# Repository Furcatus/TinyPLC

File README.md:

# TinyPLC

NOTE: This project is under construction. Do not expect everything to work just yet.

## What is it?
This project provides a small and easy-to-use open-source PLC (programmable logic controller) hardware / software platform intended for small automation and control tasks, built around a Raspberry Pi Pico 2W.

## Who is it for?
TinyPLC aims towards hobbyist developers and electrical engineers who want to easily automate stuff in the physical world with Python, but have been limited due to the lack of peripheral hardware connected to their microcontrollers, until now!

### Hardware features:
- 5V supply voltage
- 4 isolated digital inputs (5V to 24V, isolated external 5V supply through DC/DC converter)
- 4 relay outputs (contact: NO, up to 230V, 10A)
- SPI interface
- I²C interface
- 6 GPIOs (3,3V)
- custom 3D printable enclosure

### Software features:
- controller programmed in MicroPython
- slim PLC framework with user-defined initialization and loop function
- open-source
- possibility to use the WiFi/Bluetooth capabilities of the used Rasperry Pi Pico 2W board to build your own wireless controller

## License and Disclaimer
This project is released under the MIT license. Feel free to use it for your projects, as long as you know what you are doing when dealing with electrics/electronics. I am not liable to any harm you are causing to yourself, others or someone's property when using the provided files. Do not use TinyPLC with dangerous voltages or for safety-critical applications and follow the regulations and laws applicable in your location!

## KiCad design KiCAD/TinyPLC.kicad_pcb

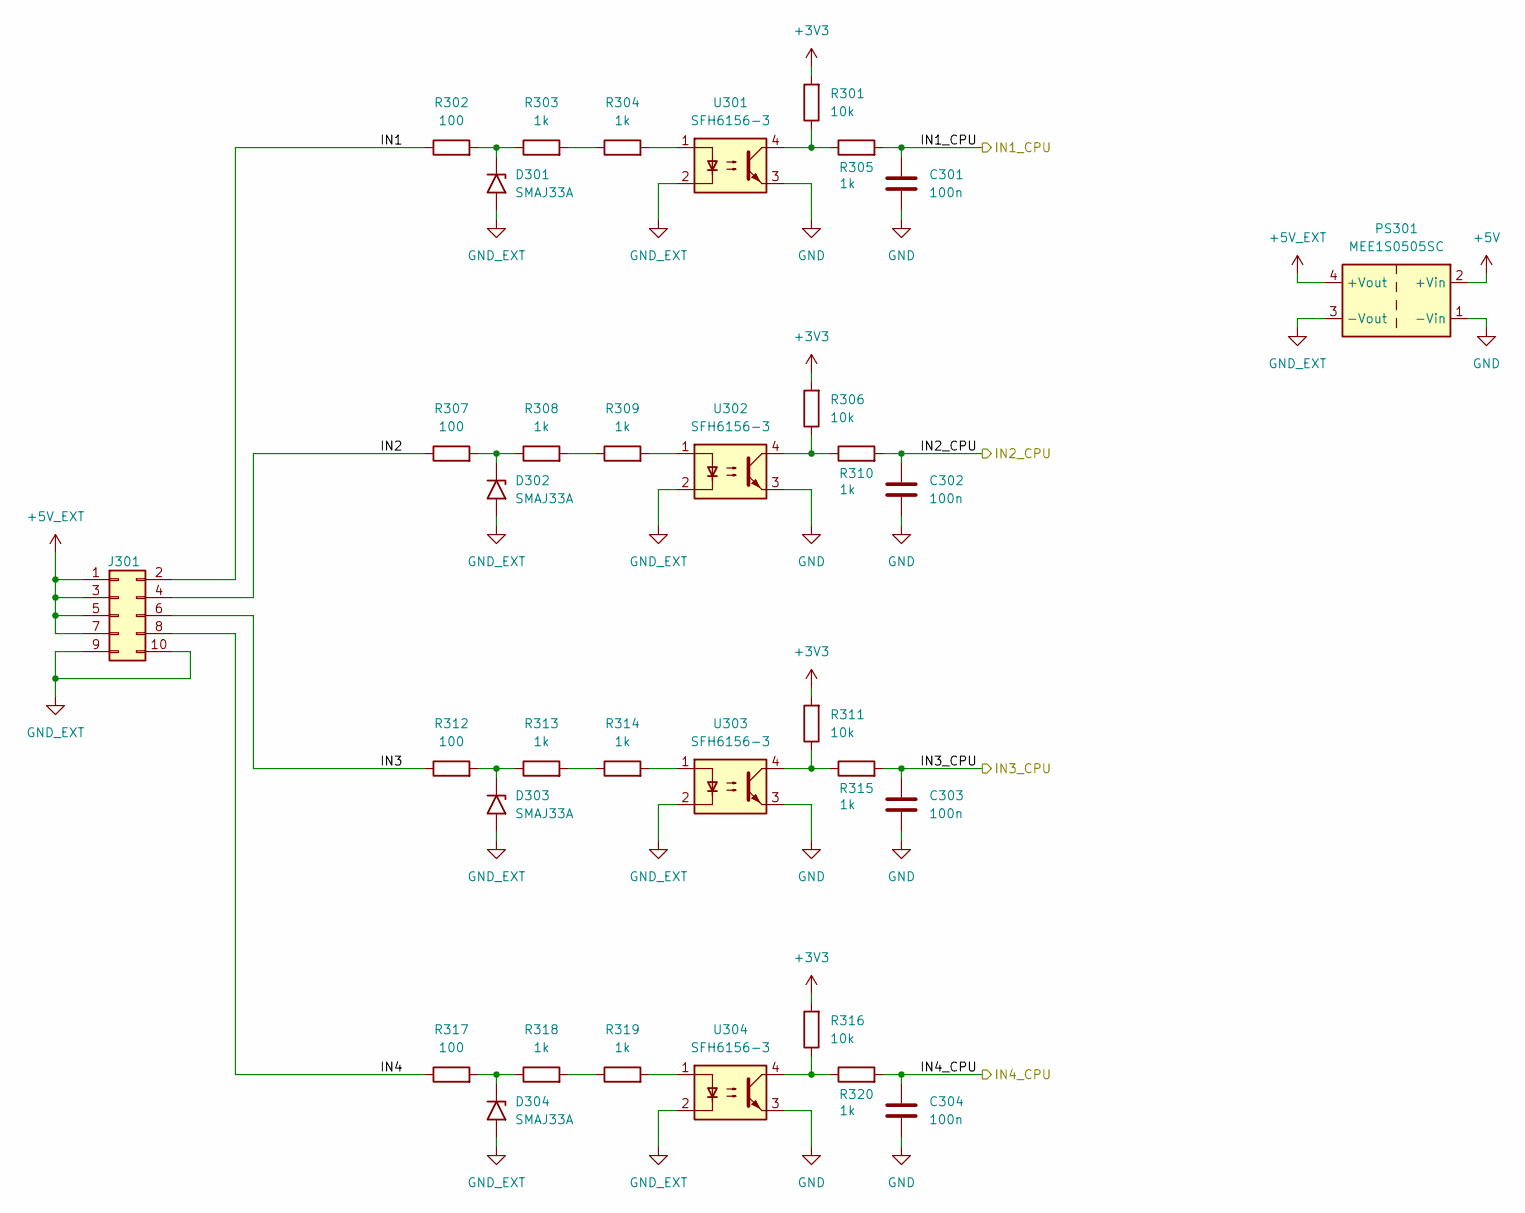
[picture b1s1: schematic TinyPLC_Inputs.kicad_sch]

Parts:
C301, C302, C303, C304: 100n; C_0603_1608Metric_Pad1.08x0.95mm_HandSolder
D301, D302, D303, D304: SMAJ33A; D_SMA
J301: S2L 3.50/10/180G 3.5SN OR BX; Weidmüller_S2L_2x05_3.50mm
PS301: MEE1S0505SC; Converter_DCDC_Murata_MEE1SxxxxSC_THT
R301, R306, R311, R316: 10k; R_0603_1608Metric_Pad0.98x0.95mm_HandSolder
R302, R307, R312, R317: 100; R_MiniMELF_MMA-0204
R303, R304, R308, R309, R313, R314, R318, R319: 1k; R_1206_3216Metric_Pad1.30x1.75mm_HandSolder
R305, R310, R315, R320: 1k; R_0603_1608Metric_Pad0.98x0.95mm_HandSolder
U301, U302, U303, U304: SFH6156-3; DIP-4_W7.62mm_SMDSocket_SmallPads

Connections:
+3V3: R301.2, R306.2, R311.2, R316.2; also elsewhere on the board
+5V: PS301.2 (+Vin); also elsewhere on the board
+5V_EXT: J301.1, J301.3, J301.5, J301.7, PS301.4 (+Vout)
/Controller/IN1_CPU: C301.1, R305.2; also elsewhere on the board
/Controller/IN2_CPU: C302.1, R310.2; also elsewhere on the board
/Controller/IN3_CPU: C303.1, R315.2; also elsewhere on the board
/Controller/IN4_CPU: C304.1, R320.2; also elsewhere on the board
/Inputs/IN1: J301.2, R302.1
/Inputs/IN2: J301.4, R307.1
/Inputs/IN3: J301.6, R312.1
/Inputs/IN4: J301.8, R317.1
GND: C301.2, C302.2, C303.2, C304.2, PS301.1 (-Vin), U301.3, U302.3, U303.3, U304.3; also elsewhere on the board
GND_EXT: D301.2 (A2), D302.2 (A2), D303.2 (A2), D304.2 (A2), J301.9, J301.10, PS301.3 (-Vout), U301.2, U302.2, U303.2, U304.2
unnamed: D301.1 (A1), R302.2, R303.1
unnamed: D302.1 (A1), R307.2, R308.1
unnamed: D303.1 (A1), R312.2, R313.1
unnamed: D304.1 (A1), R317.2, R318.1
unnamed: R301.1, R305.1, U301.4
unnamed: R303.2, R304.1
unnamed: R304.2, U301.1
unnamed: R306.1, R310.1, U302.4
unnamed: R308.2, R309.1
unnamed: R309.2, U302.1
unnamed: R311.1, R315.1, U303.4
unnamed: R313.2, R314.1
unnamed: R314.2, U303.1
unnamed: R316.1, R320.1, U304.4
unnamed: R318.2, R319.1
unnamed: R319.2, U304.1

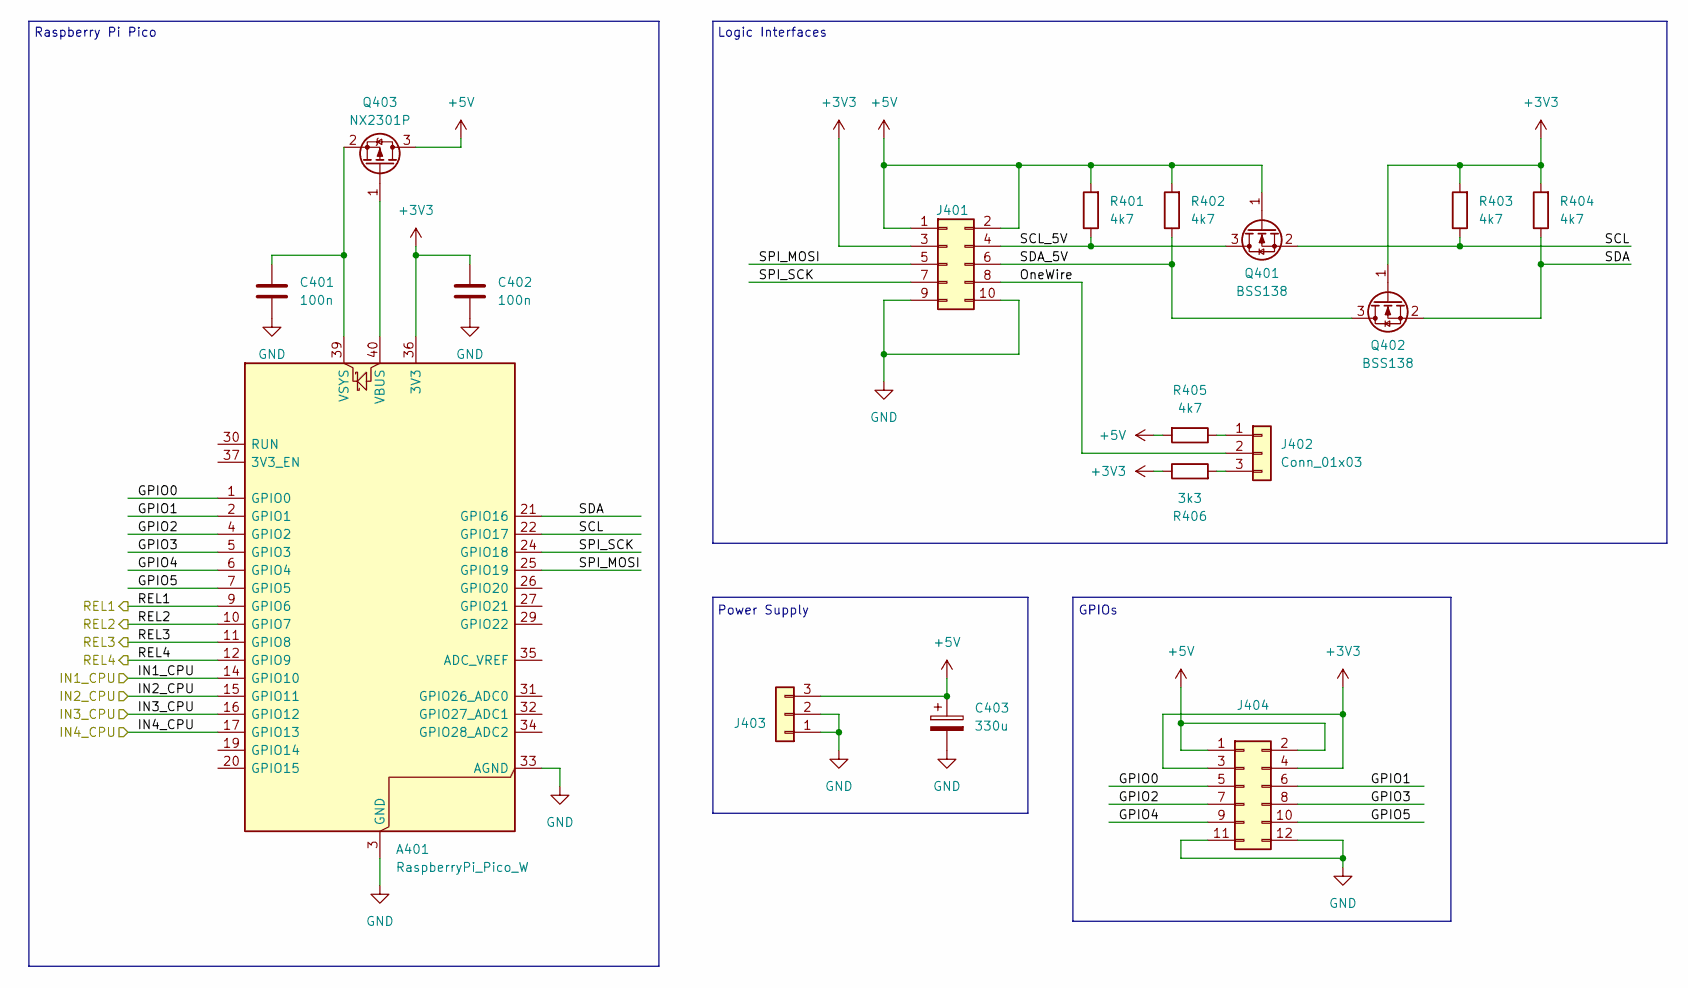
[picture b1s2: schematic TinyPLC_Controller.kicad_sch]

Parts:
A401: RaspberryPi_Pico_W; RaspberryPi_Pico_Common_SMD
C401, C402: 100n; C_0603_1608Metric_Pad1.08x0.95mm_HandSolder
C403: 330u; CP_Elec_6.3x5.9
J401: S2L 3.50/10/180G 3.5SN OR BX; Weidmüller_S2L_2x05_3.50mm
J402: Conn_01x03; PinHeader_1x03_P2.54mm_Vertical
J403: S2L 3.50/03/180G 3.2SN OR BX; Weidmüller_S2L_1x03_3.50mm
J404: Conn_02x06_Odd_Even; PinSocket_2x06_P2.54mm_Vertical
Q401, Q402: BSS138; SOT-23-3
Q403: NX2301P; SOT-23
R401, R402, R403, R404, R405: 4k7; R_0603_1608Metric_Pad0.98x0.95mm_HandSolder
R406: 3k3; R_0603_1608Metric_Pad0.98x0.95mm_HandSolder

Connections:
+3V3: A401.36 (3V3), C402.1, J401.3, J404.3, J404.4, Q402.1 (G), R403.2, R404.2, R406.1; also elsewhere on the board
+5V: C403.1, J401.1, J401.2, J403.3, J404.1, J404.2, Q401.1 (G), Q403.3 (D), R401.2, R402.2, R405.2; also elsewhere on the board
/Controller/GPIO0: A401.1 (GPIO0), J404.5
/Controller/GPIO1: A401.2 (GPIO1), J404.6
/Controller/GPIO2: A401.4 (GPIO2), J404.7
/Controller/GPIO3: A401.5 (GPIO3), J404.8
/Controller/GPIO4: A401.6 (GPIO4), J404.9
/Controller/GPIO5: A401.7 (GPIO5), J404.10
/Controller/IN1_CPU: A401.14 (GPIO10); also elsewhere on the board
/Controller/IN2_CPU: A401.15 (GPIO11); also elsewhere on the board
/Controller/IN3_CPU: A401.16 (GPIO12); also elsewhere on the board
/Controller/IN4_CPU: A401.17 (GPIO13); also elsewhere on the board
/Controller/OneWire: J401.8, J402.2
/Controller/REL1: A401.9 (GPIO6); also elsewhere on the board
/Controller/REL2: A401.10 (GPIO7); also elsewhere on the board
/Controller/REL3: A401.11 (GPIO8); also elsewhere on the board
/Controller/REL4: A401.12 (GPIO9); also elsewhere on the board
/Controller/SCL: A401.22 (GPIO17), Q401.2 (S), R403.1
/Controller/SCL_5V: J401.4, Q401.3 (D), R401.1
/Controller/SDA: A401.21 (GPIO16), Q402.2 (S), R404.1
/Controller/SDA_5V: J401.6, Q402.3 (D), R402.1
/Controller/SPI_MOSI: A401.25 (GPIO19), J401.5
/Controller/SPI_SCK: A401.24 (GPIO18), J401.7
GND: A401.3 (GND), A401.8 (GND), A401.13 (GND), A401.18 (GND), A401.23 (GND), A401.28 (GND), A401.33 (AGND), A401.38 (GND), C401.2, C402.2, C403.2, J401.9, J401.10, J403.1, J403.2, J404.11, J404.12; also elsewhere on the board
unnamed: A401.40 (VBUS), Q403.1 (G)
unnamed: A401.39 (VSYS), C401.1, Q403.2 (S)
unnamed: J402.1, R405.1
unnamed: J402.3, R406.2

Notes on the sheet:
Power Supply
GPIOs
Logic Interfaces
Raspberry Pi Pico

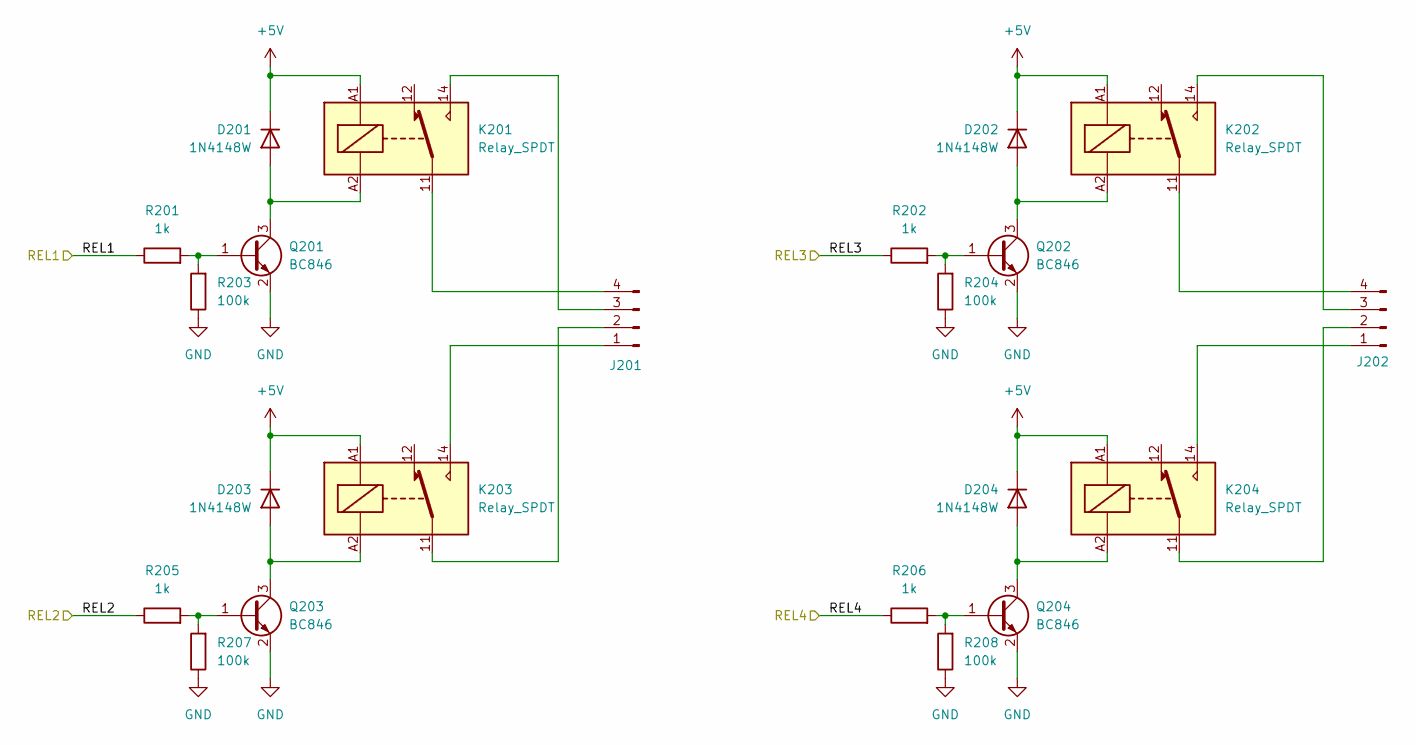
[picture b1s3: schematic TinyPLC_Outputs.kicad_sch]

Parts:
D201, D202, D203, D204: 1N4148W; D_SOD-123
J201, J202: Conn_01x04_Pin; PhoenixContact_MSTBVA_2,5_4-G-5,08_1x04_P5.08mm_Vertical
K201, K202, K203, K204: Relay_SPDT; Relay_SPDT_Hongfa_HF118F
Q201, Q202, Q203, Q204: BC846; SOT-23-3
R201, R202, R205, R206: 1k; R_0603_1608Metric_Pad0.98x0.95mm_HandSolder
R203, R204, R207, R208: 100k; R_0603_1608Metric_Pad0.98x0.95mm_HandSolder

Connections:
+5V: D201.1 (K), D202.1 (K), D203.1 (K), D204.1 (K), K201.A1, K202.A1, K203.A1, K204.A1; also elsewhere on the board
/Controller/REL1: R201.1; also elsewhere on the board
/Controller/REL2: R205.1; also elsewhere on the board
/Controller/REL3: R202.1; also elsewhere on the board
/Controller/REL4: R206.1; also elsewhere on the board
GND: Q201.2 (E), Q202.2 (E), Q203.2 (E), Q204.2 (E), R203.1, R204.1, R207.1, R208.1; also elsewhere on the board
unnamed: D201.2 (A), K201.A2, Q201.3 (C)
unnamed: D202.2 (A), K202.A2, Q202.3 (C)
unnamed: D203.2 (A), K203.A2, Q203.3 (C)
unnamed: D204.2 (A), K204.A2, Q204.3 (C)
unnamed: J201.1, K203.14
unnamed: J201.2, K203.11
unnamed: J201.3, K201.14
unnamed: J201.4, K201.11
unnamed: J202.1, K204.14
unnamed: J202.2, K204.11
unnamed: J202.3, K202.14
unnamed: J202.4, K202.11
unnamed: Q201.1 (B), R201.2, R203.2
unnamed: Q202.1 (B), R202.2, R204.2
unnamed: Q203.1 (B), R205.2, R207.2
unnamed: Q204.1 (B), R206.2, R208.2

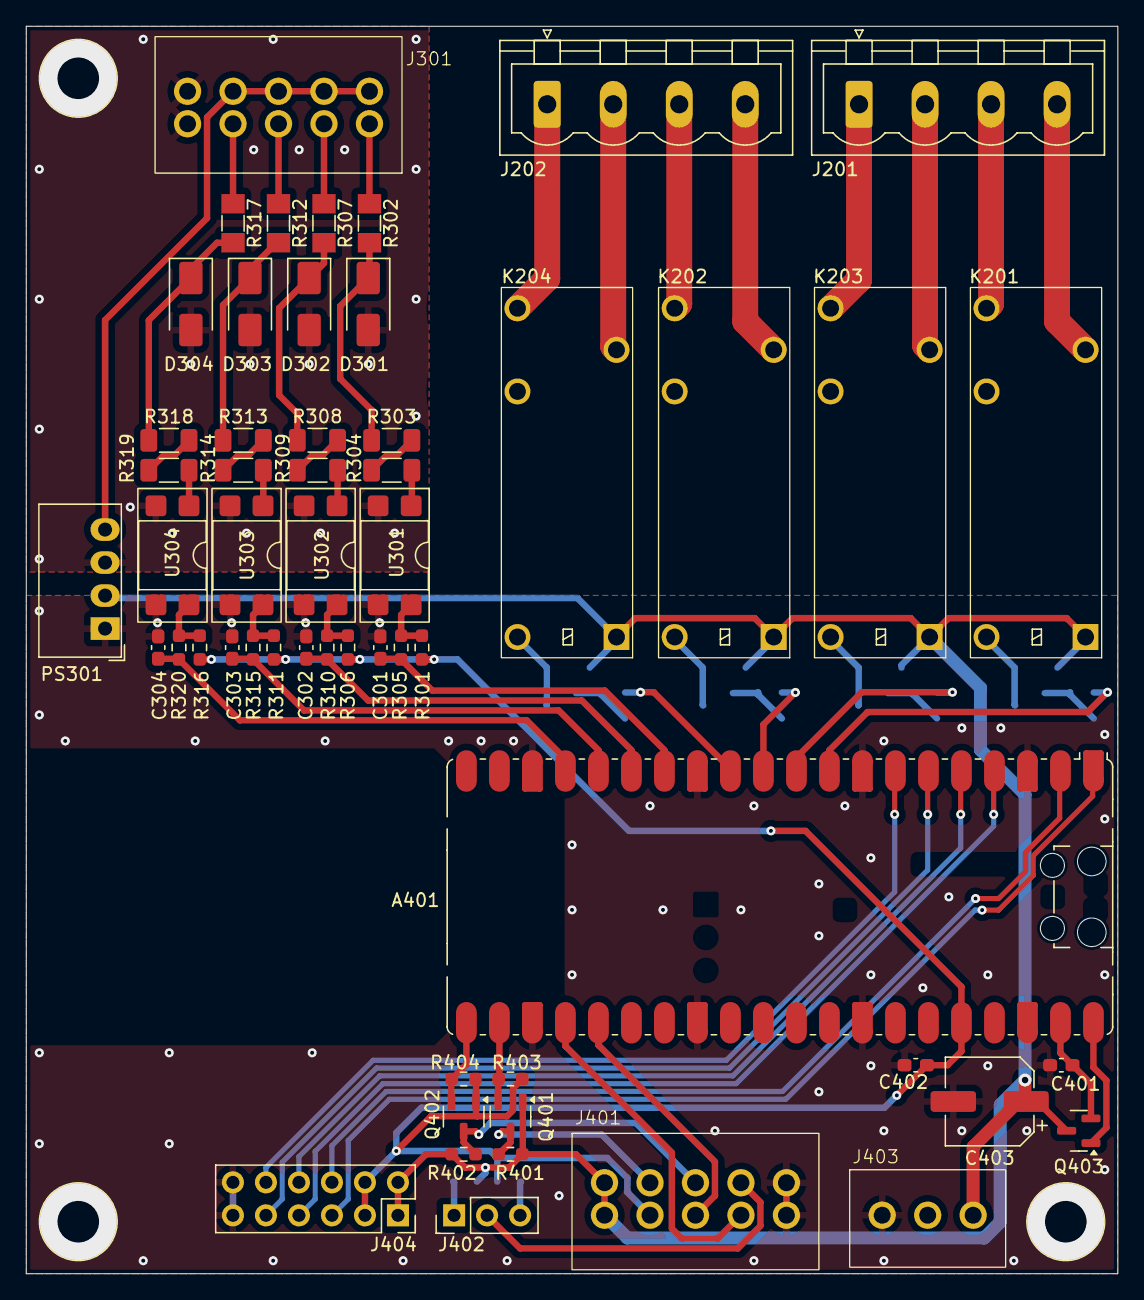
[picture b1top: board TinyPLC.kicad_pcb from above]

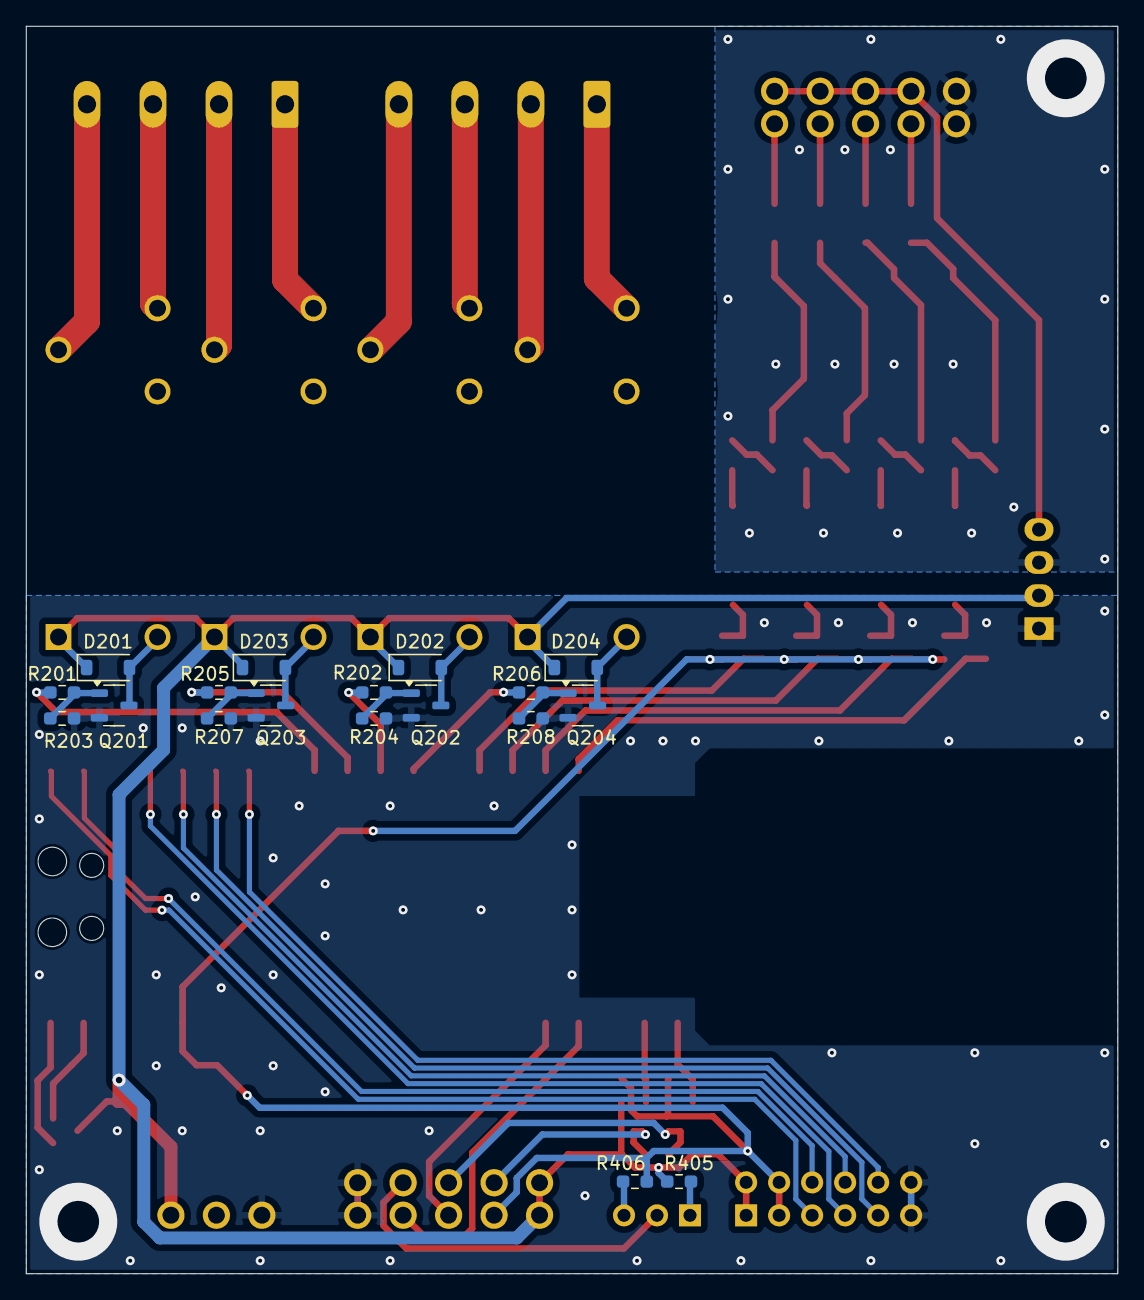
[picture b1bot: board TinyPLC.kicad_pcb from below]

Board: 2 copper layers, 84.0 x 96.0 mm, 73 parts (18 on the bottom side), 66 nets.

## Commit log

2025-11-15 Added under construction note
2025-11-15 initial release of code
2025-11-15 added KiCAD files
2025-11-16 - uploaded the correct files, I/Os and I2C is now working - included a sample implementation for AHT20 sensor with external library (credit and license in the file itself)
2025-11-21 Added attribution for used library, added gitignore file
